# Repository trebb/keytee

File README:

keytee -- Controller breakout board for small keyboards

Keytee is based on the ATMEGA32U2 controller.  With its 20 usable I/O
pins, it can drive keyboards with up to 100 keys.  The PCB is intended
to sit between the switches of a mechanical keyboard, not adding any
bulk; cf. http://imgur.com/v3vOg1i.

./pcb/ contains the hardware design as a KiCAD project.

TMK-based ./firmware/ defines a 10-row, 10-column keymap with a total
of 10 keys that exercise all the hardware pins.  It is meant for
hardware testing and should probably adapted to any specific
requirements.

Generated bootloaders, firmware, Gerber files, etc. can be found at
https://trebb.github.io/keytee.

https://deskthority.net/workshop-f7/keytee-controller-breakout-board-for-small-keyboards-t15586.html

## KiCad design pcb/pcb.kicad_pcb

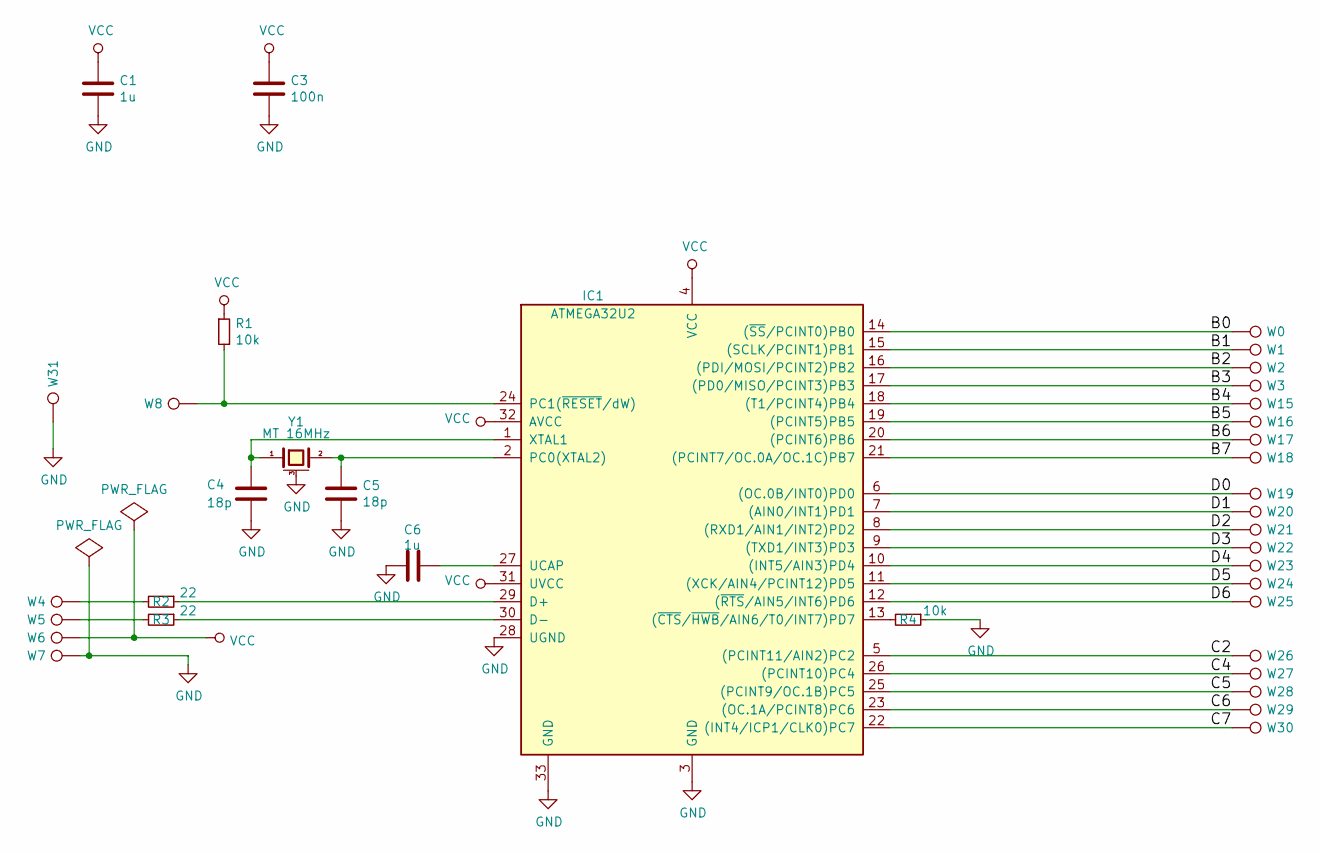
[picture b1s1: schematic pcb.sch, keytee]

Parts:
C1, C6: 1u; C_0402_square
C3: 100n; C_0402_square
C4, C5: 18p; C_0402_square
IC1: ATMEGA32U2; QFN-32-1EP_5x5mm_Pitch0.5mm_internal_vias
R1, R4: 10k; R_0402_square
R2, R3: 22; R_0402_square
W0, W1, W2, W3, W4, W5, W6, W7, W8, W15, W16, W17, W18, W19, W20, W21, W22, W23, W24, W25, W26, W27, W28, W29, W30: TEST_1P; SolderWirePad_SMD
W31: TEST_1P; SolderWirePad_SMD_circular
Y1: MT 16MHz; crystal_MT_32x25

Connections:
/B0: IC1.14 ((~SS~/PCINT0)PB0), W0.1
/B1: IC1.15 ((SCLK/PCINT1)PB1), W1.1
/B2: IC1.16 ((PDI/MOSI/PCINT2)PB2), W2.1
/B3: IC1.17 ((PD0/MISO/PCINT3)PB3), W3.1
/B4: IC1.18 ((T1/PCINT4)PB4), W15.1
/B5: IC1.19 ((PCINT5)PB5), W16.1
/B6: IC1.20 ((PCINT6)PB6), W17.1
/B7: IC1.21 ((PCINT7/OC.0A/OC.1C)PB7), W18.1
/C2: IC1.5 ((PCINT11/AIN2)PC2), W26.1
/C4: IC1.26 ((PCINT10)PC4), W27.1
/C5: IC1.25 ((PCINT9/OC.1B)PC5), W28.1
/C6: IC1.23 ((OC.1A/PCINT8)PC6), W29.1
/C7: IC1.22 ((INT4/ICP1/CLK0)PC7), W30.1
/D0: IC1.6 ((OC.0B/INT0)PD0), W19.1
/D1: IC1.7 ((AIN0/INT1)PD1), W20.1
/D2: IC1.8 ((RXD1/AIN1/INT2)PD2), W21.1
/D3: IC1.9 ((TXD1/INT3)PD3), W22.1
/D4: IC1.10 ((INT5/AIN3)PD4), W23.1
/D5: IC1.11 ((XCK/AIN4/PCINT12)PD5), W24.1
/D6: IC1.12 ((~RTS~/AIN5/INT6)PD6), W25.1
GND: C1.2, C3.2, C4.2, C5.2, C6.1, IC1.3 (GND), IC1.28 (UGND), IC1.33 (GND), R4.1, W7.1, W31.1, Y1.3 (case)
unnamed: C4.1, IC1.1 (XTAL1), Y1.1
unnamed: C5.1, IC1.2 (PC0(XTAL2)), Y1.2
unnamed: C6.2, IC1.27 (UCAP)
unnamed: IC1.13 ((~CTS~/~HWB~/AIN6/T0/INT7)PD7), R4.2
unnamed: IC1.24 (PC1(~RESET~/dW)), R1.2, W8.1
unnamed: IC1.29 (D+), R2.1
unnamed: IC1.30 (D-), R3.1
unnamed: R2.2, W4.1
unnamed: R3.2, W5.1
VCC: C1.1, C3.1, IC1.4 (VCC), IC1.31 (UVCC), IC1.32 (AVCC), R1.1, W6.1

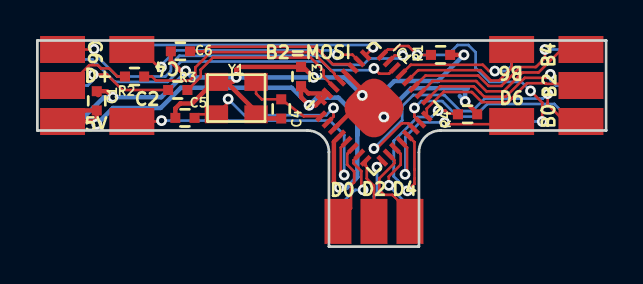
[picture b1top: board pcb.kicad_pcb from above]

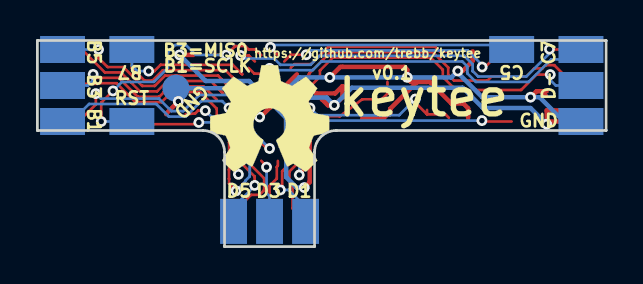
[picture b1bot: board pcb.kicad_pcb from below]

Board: 2 copper layers, 31.6 x 11.5 mm, 37 parts (13 on the bottom side), 31 nets.

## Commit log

2016-12-07 Tweak USB tracks to resemble a differential pair
2016-12-13 Adapt to manufacturer's capabilities
2017-02-05 Fix firmware including bootloader
    We now have a minimal testing keymap.
2017-02-05 Add README and a way to upload generated project files
2017-02-05 Fix image link in README
2017-02-07 More generated files
2017-02-09 keytee has its own USB PID, issued by http://pid.codes: 0xE4EE
2017-02-09 gh-pages pseudo commit
2017-02-11 README: add keymap and an ascii-art pinout map
